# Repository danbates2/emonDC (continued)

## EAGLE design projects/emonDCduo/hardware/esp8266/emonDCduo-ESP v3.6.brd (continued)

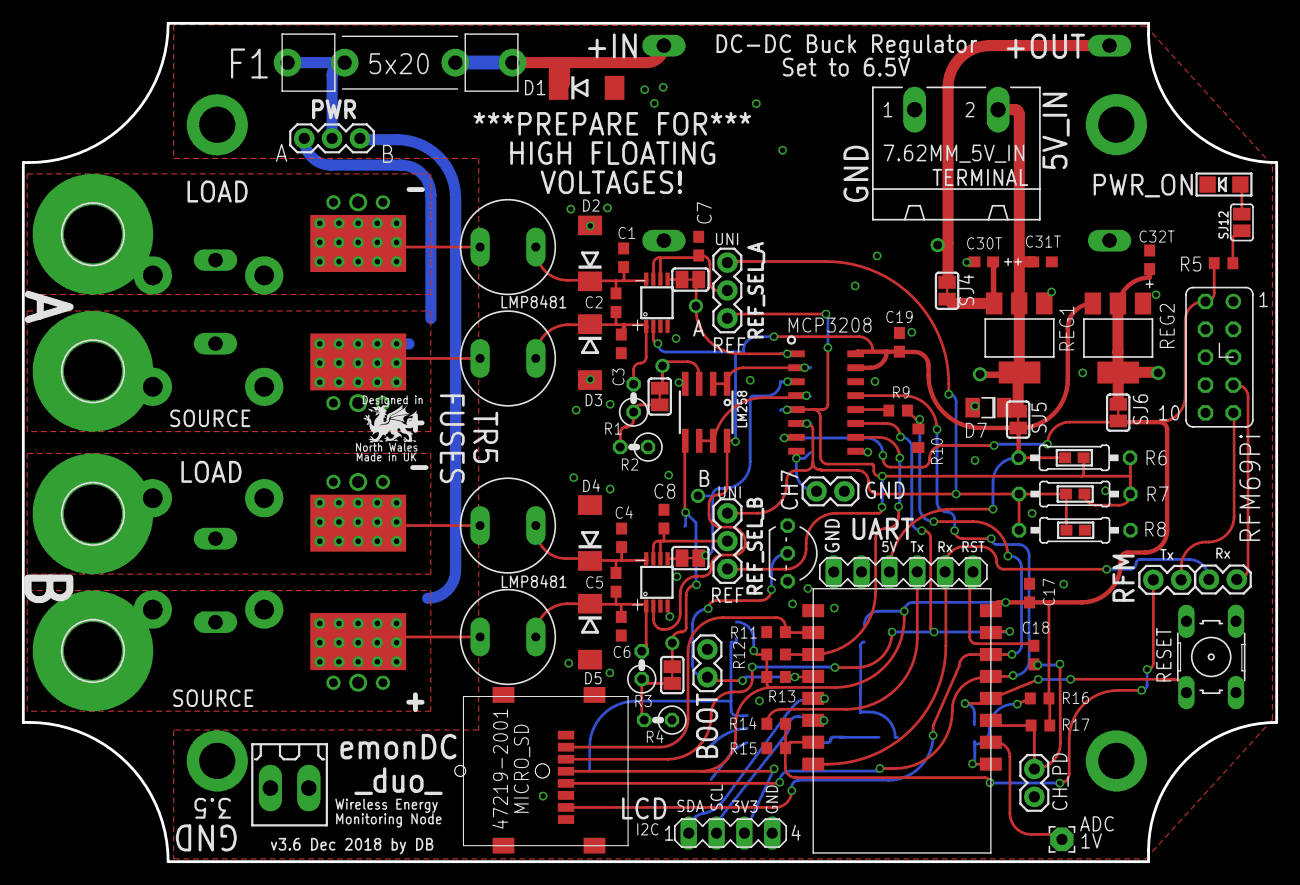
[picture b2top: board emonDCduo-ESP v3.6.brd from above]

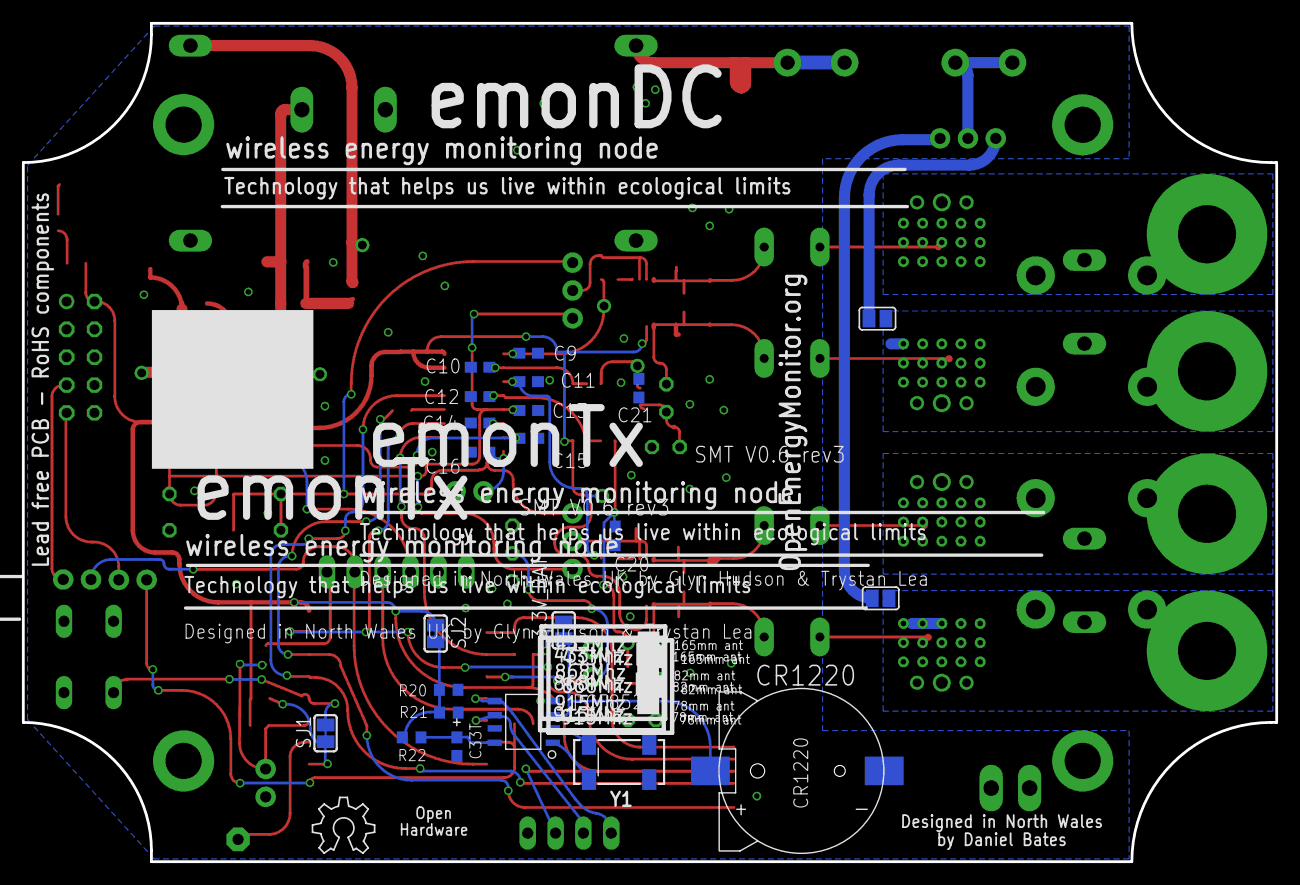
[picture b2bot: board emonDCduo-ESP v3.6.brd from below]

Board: 2 copper layers, 114.3 x 76.5 mm, 126 parts (24 on the bottom side), 60 nets.

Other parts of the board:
U$2, U$3: ALIGNMENT_STOP

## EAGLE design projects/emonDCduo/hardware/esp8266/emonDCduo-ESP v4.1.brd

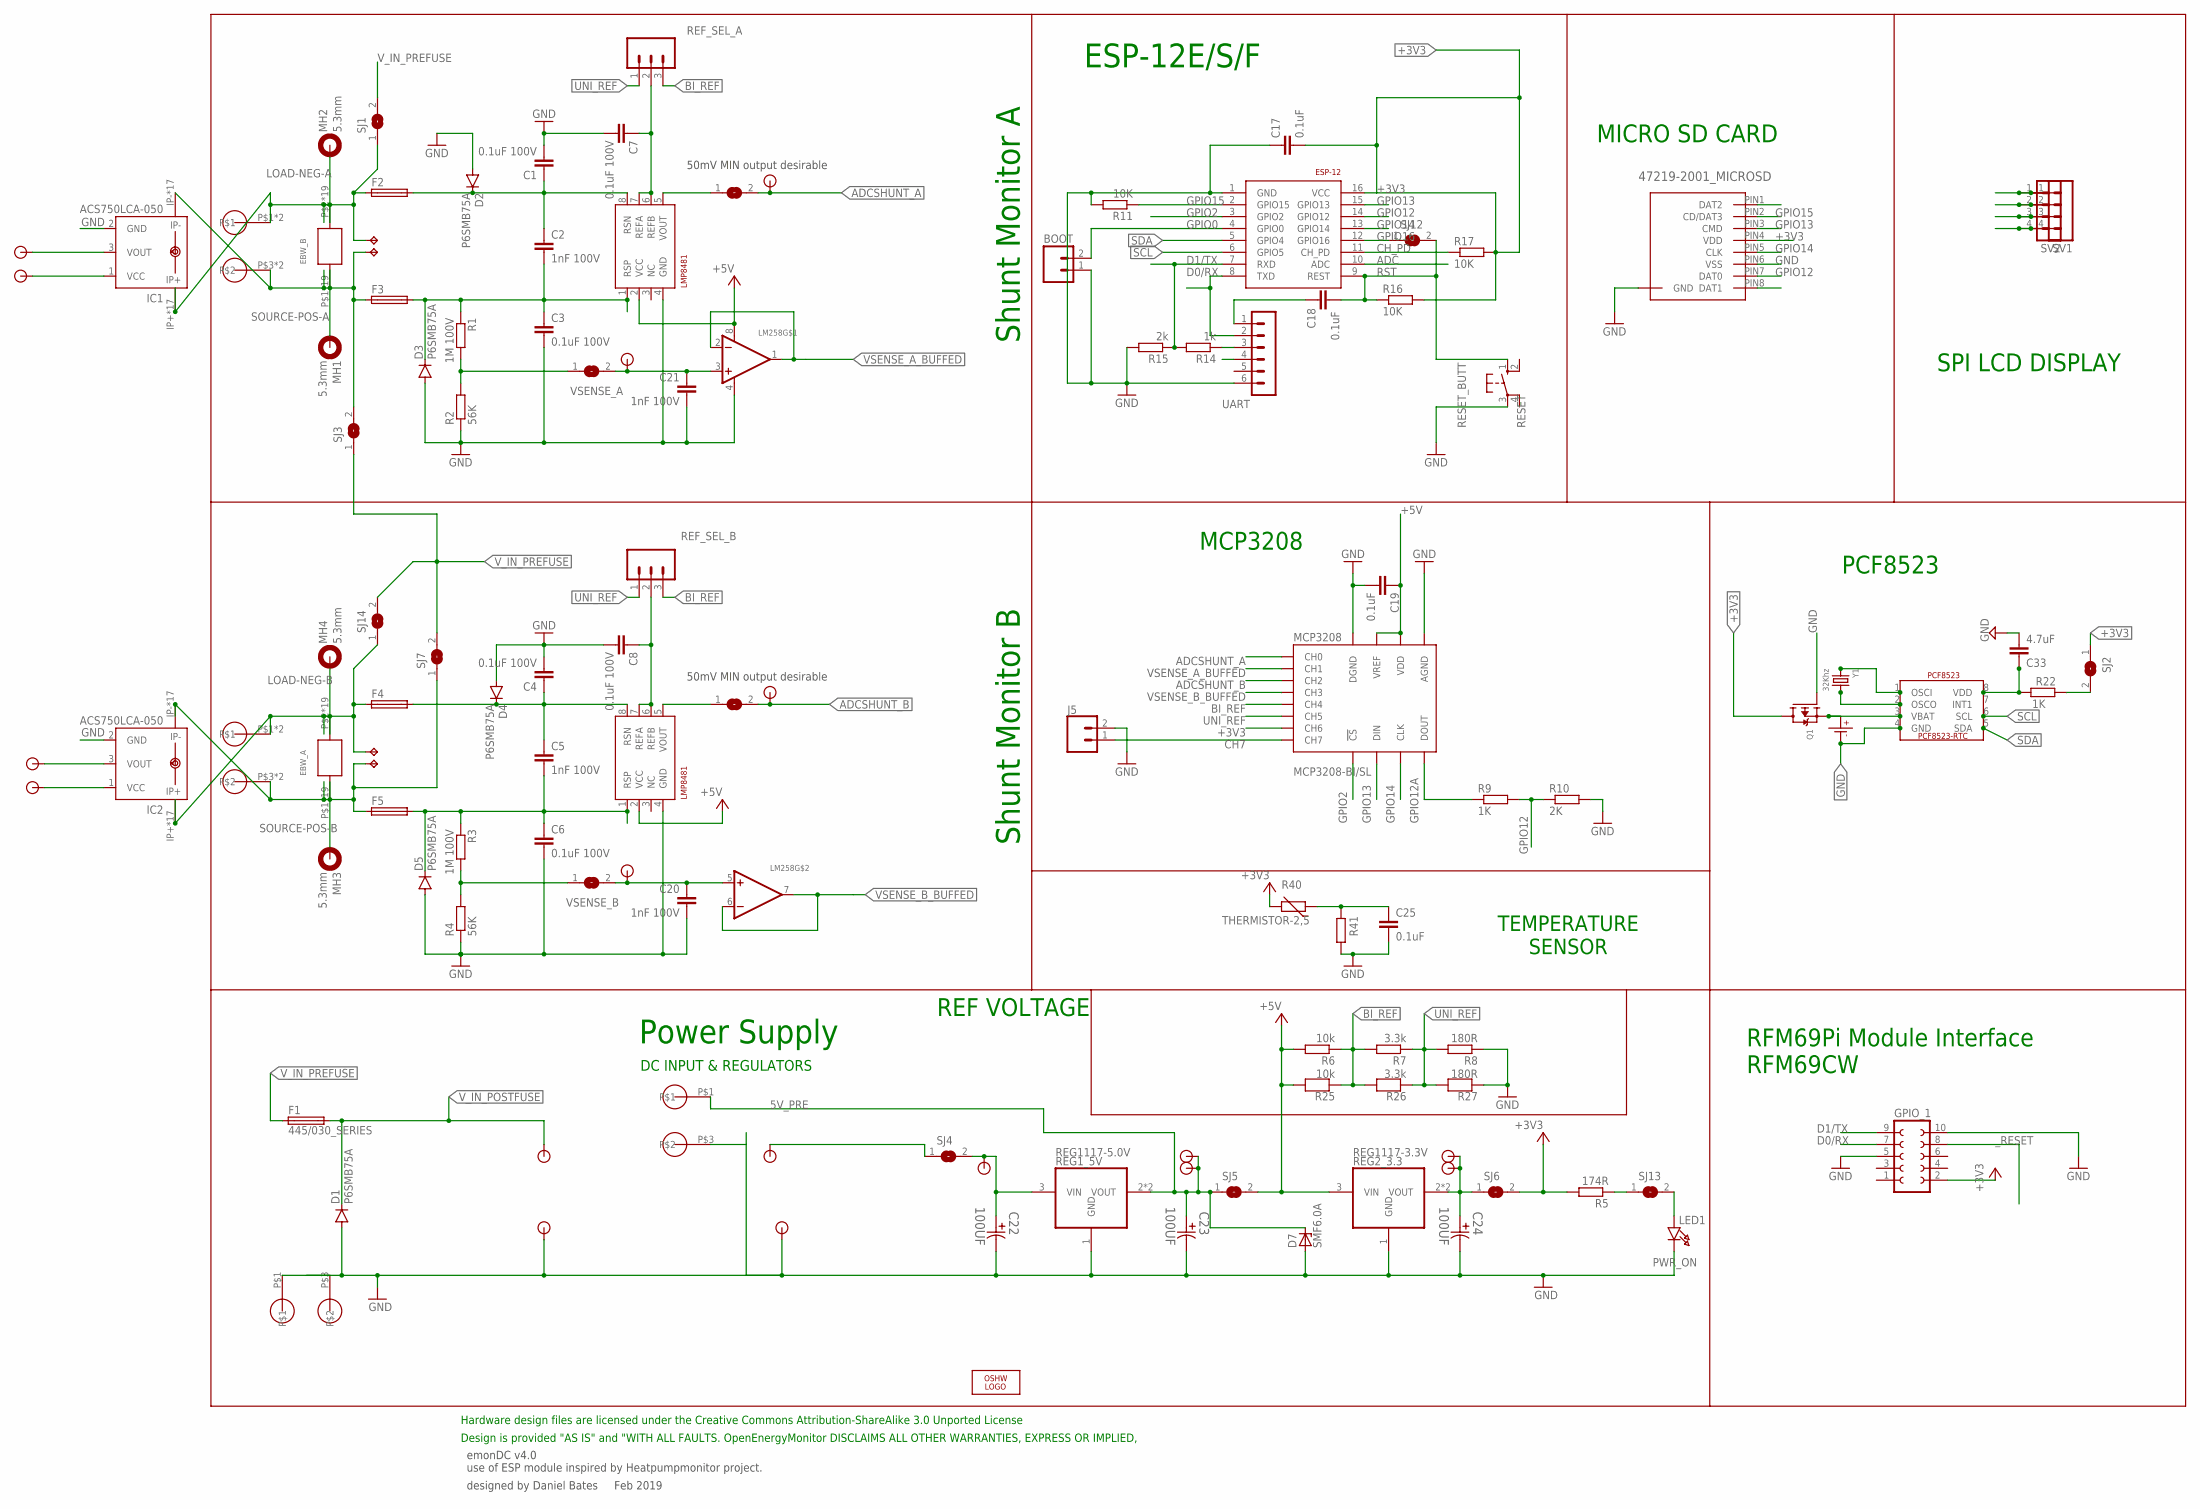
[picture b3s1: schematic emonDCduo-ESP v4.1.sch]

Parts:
BOOT: M02PTH; 1X02
C1, C3, C4, C6, C7, C8: 0.1uF 100V; C0805; MPN C1608X7S2A104K080AB
C2, C5, C20, C21: 1nF 100V; C0805; MPN C1608X7S2A104K080AB
C17, C18, C19, C25: 0.1uF; C0805
C22, C23, C24: 100UF; CAPAE530X610N
C33: 4.7uF; C0805
CR1220: CR1220SMD; MPN Harwin S8411-45R
D1: P6SMB75A; DO214AA
D2, D3, D4, D5: P6SMB75A; SMB
D7: SMF6.0A; SOD123F
EBW_A: EBW_SERIES_15.2MM
EBW_B: EBW_SERIES_15.2MM
ESP-12: ESP8266_ESP-12; ESP8266-ESP12
F1: 445/030_SERIES; 445/030_SERIES_LITTELFUSE
F2, F3, F4, F5: TR5
GPIO_1: FE05-2_RFM69PI_OUTLINERFM69PI; FE05-2_RFM69PI_OULTINE
IC1, IC2: ACS750LCA-050; ACS75050
J5: CONN_02; 1X02
LED1: PWR_ON; CHIPLED_1206
LM258: LM358; SOIC8_150MIL
LOGO1: OSHW_LOGO_6MILX0200-NT; OSHW_6X200_NOTEXT
MCP3208: MCP3208-BI/SL; SOIC16
MH1, MH2, MH3, MH4: 5.3mm; 5,3//11-PAD
MICRO_SD: 47219-2001_MICROSD
MOUNT_10.16_A, MOUNT_10.16_B: MOLEX_39970-003; 2/10,16
PCF8523: PCF8523_RTC; SOIC_8
Q1: MOSFET-P; SOT23-R
R1, R3: 1M 100V; 0207/2V; MPN MCMF006FF1004A50
R2, R4: 56K; 0207/2V; MPN MCMF006FF7502A50
R5: 174R; R0603
R6: 10k; 0207/10
R7: 3.3k; 0207/10
R8: 180R; 0207/10
R9: 1K; R0603; MPN MCWR06X5901FTL
R10: 2K; R0603; MPN MCWR06X5901FTL
R11, R16, R17: 10K; R0603
R14: 1k; R0603
R15: 2k; R0603
R22: 1K; R0603
R25: 10k; 0603
R26: 3.3k; 0603
R27: 180R; 0603
R40: THERMISTOR-2,5; RS-2,5
R41: R-EU_0207/2V; 0207/2V
REF_SEL_A: 455-1750-1-ND; 1X03; MPN 2212S-02SG-85
REF_SEL_B: 455-1750-1-ND; 1X03; MPN 2212S-02SG-85
REG1_5V: REG1117-5.0V; SOT223; MPN REG1117-5.0
REG2_3.3: REG1117-3.3V; SOT223; MPN REG1117-3.3
RESET: RESET_BUTT; B3F-10XX; MPN FSM4JH
SHUNTMON-A: LMP8481; S-PDSO-G08; MPN LMP8481MME-S/NOPB
SHUNTMON-B: LMP8481; S-PDSO-G08; MPN LMP8481MME-H/NOPB
SJ1, SJ3, SJ7, SJ14: SJW
SJ2, SJ4, SJ5, SJ6, SJ8, SJ9, SJ10, SJ11, SJ12, SJ13: SOLDERJUMPERCLOSED; SOLDERJUMPER_CLOSEDWIRE
SV1, SV2: MA04-1; MPN 2212S-04SG-85
TP8, TP9, TP10, TP11: TPPAD1-13Y; P1-13Y
U$1, U$4, U$5, U$6, U$7, U$8, U$9, U$14, U$15, U$16, U$17, U$18, U$19: TP0.8MM; TP0.8
U$2, U$3, U$10, U$11: 2212S-02SG-85; TP0.8_X2
U$12, U$13: 5MMBLOCK; 2/5.08
UART: UART; MA06-1
Y1: 32Khz; CRYSTAL_8X3.8

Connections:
3.3V_PRE: C24.1, REG2_3.3.2 (VOUT), REG2_3.3.4 (VOUT), SJ6.1, U$8.P$1, U$19.P$1
5V_PRE: C23.1, D7.C, REG1_5V.2 (VOUT), REG1_5V.4 (VOUT), SJ5.1, U$7.P$1, U$12.P$1, U$18.P$1
6.5V: C22.1, REG1_5V.3 (VIN), SJ4.2, U$9.P$1
+3V3: C17.2, ESP-12.16 (VCC), GPIO_1.2, MCP3208.7 (CH6), MICRO_SD.PIN4 (VDD), Q1.3 (D), R5.2, R16.2, R17.2, R40.2, SJ2.1, SJ6.2, SV1.3, SV2.3
+5V: C19.1, LM258.8 (V+), MCP3208.15 (VREF), MCP3208.16 (VDD), R6.2, R25.2, REG2_3.3.3 (VIN), SHUNTMON-A.2 (VCC), SHUNTMON-B.2 (VCC), SJ5.2, UART.4
ADC: C25.1, ESP-12.10 (ADC), R40.1, R41.2
ADCSHUNT_A: MCP3208.1 (CH0), SJ11.2, U$6.P$1
ADCSHUNT_B: MCP3208.3 (CH2), SJ10.2, U$5.P$1
BI_REF: MCP3208.5 (CH4), R6.1, R7.2, R25.1, R26.2, REF_SEL_A.3, REF_SEL_B.3
CH7: J5.1, MCP3208.8 (CH7)
CH_PD: ESP-12.11 (CH_PD), R17.1
D0/RX: ESP-12.8 (TXD), GPIO_1.7, UART.2
D1/TX: ESP-12.7 (RXD), GPIO_1.9, R14.2, R15.1
GND: BOOT.1, C1.2, C3.2, C4.2, C6.2, C7.2, C8.2, C17.1, C19.2, C20.2, C21.2, C22.2, C23.2, C24.2, C25.2, C33.2, CR1220.P- (P$-), D1.A, D2.A, D3.A, D4.A, D5.A, D7.A, ESP-12.1 (GND), GPIO_1.5, GPIO_1.10, IC1.2 (GND), IC2.2 (GND), J5.2, LED1.C, LM258.4 (V-), MCP3208.9 (DGND), MCP3208.14 (AGND), MICRO_SD.P$1 (GND), MICRO_SD.P$2 (GND), MICRO_SD.P$3 (GND), MICRO_SD.P$4 (GND), MICRO_SD.PIN6 (VSS), PCF8523.4 (GND), Q1.1 (G), R2.1, R4.1, R8.1, R10.2, R11.2, R15.2, R27.1, R41.1, REG1_5V.1 (GND), REG2_3.3.1 (GND), RESET.3, SHUNTMON-A.4 (GND), SHUNTMON-B.4 (GND), SV1.4, SV2.4, U$3.P$1, U$3.P$2, U$11.P$1, U$11.P$2, U$12.P$3, U$13.P$1, U$13.P$3, UART.6
GPIO0: BOOT.2, ESP-12.4 (GPIO0)
GPIO2: ESP-12.3 (GPIO2), MCP3208.10 (!CS)
GPIO12: ESP-12.14 (GPIO12), MICRO_SD.PIN7 (DAT0), R9.2, R10.1
GPIO12A: MCP3208.12 (DOUT), R9.1
GPIO13: ESP-12.15 (GPIO13), MCP3208.11 (DIN), MICRO_SD.PIN3 (CMD)
GPIO14: ESP-12.13 (GPIO14), MCP3208.13 (CLK), MICRO_SD.PIN5 (CLK)
GPIO15: ESP-12.2 (GPIO15), MICRO_SD.PIN2 (CD/DAT3), R11.1
GPIO16: ESP-12.12 (GPIO16), SJ12.1
LOAD-NEG-A: EBW_B.P$2, EBW_B.P$18, EBW_B.P$19, EBW_B.P$20, EBW_B.P$21, EBW_B.P$22, EBW_B.P$23, EBW_B.P$24, EBW_B.P$25, EBW_B.P$26, EBW_B.P$27, EBW_B.P$28, EBW_B.P$29, EBW_B.P$30, EBW_B.P$31, EBW_B.P$32, EBW_B.P$36, EBW_B.P$37, EBW_B.P$38, F2.1, IC1.IP+, IC1.IP+@2 (IP+), IC1.IP+@3 (IP+), IC1.IP+@4 (IP+), IC1.IP+@5 (IP+), IC1.IP+@6 (IP+), IC1.IP+@7 (IP+), IC1.IP+@8 (IP+), IC1.IP+@9 (IP+), IC1.IP+@10 (IP+), IC1.IP+@11 (IP+), IC1.IP+@12 (IP+), IC1.IP+@13 (IP+), IC1.IP+@14 (IP+), IC1.IP+@15 (IP+), IC1.IP+@16 (IP+), IC1.IP+@17 (IP+), MH2.B5,5, MOUNT_10.16_A.P$1, MOUNT_10.16_A.P$2, SJ1.1, TP11.TP
LOAD-NEG-A_T: C1.1, C2.1, D2.C, F2.2, SHUNTMON-A.8 (RSN)
LOAD-NEG-B: EBW_A.P$2, EBW_A.P$18, EBW_A.P$19, EBW_A.P$20, EBW_A.P$21, EBW_A.P$22, EBW_A.P$23, EBW_A.P$24, EBW_A.P$25, EBW_A.P$26, EBW_A.P$27, EBW_A.P$28, EBW_A.P$29, EBW_A.P$30, EBW_A.P$31, EBW_A.P$32, EBW_A.P$36, EBW_A.P$37, EBW_A.P$38, F4.1, IC2.IP+, IC2.IP+@2 (IP+), IC2.IP+@3 (IP+), IC2.IP+@4 (IP+), IC2.IP+@5 (IP+), IC2.IP+@6 (IP+), IC2.IP+@7 (IP+), IC2.IP+@8 (IP+), IC2.IP+@9 (IP+), IC2.IP+@10 (IP+), IC2.IP+@11 (IP+), IC2.IP+@12 (IP+), IC2.IP+@13 (IP+), IC2.IP+@14 (IP+), IC2.IP+@15 (IP+), IC2.IP+@16 (IP+), IC2.IP+@17 (IP+), MH4.B5,5, MOUNT_10.16_B.P$1, MOUNT_10.16_B.P$2, SJ14.1, TP9.TP
LOAD-NEG-B_T: C4.1, C5.1, D4.C, F4.2, SHUNTMON-B.8 (RSN)
unnamed: C18.1, UART.1
unnamed: R5.1, SJ13.1
unnamed: LED1.A, SJ13.2
unnamed: SHUNTMON-B.5 (VOUT), SJ10.1
unnamed: SHUNTMON-A.5 (VOUT), SJ11.1
unnamed: R14.1, UART.3
unnamed: PCF8523.2 (OSCO), Y1.P$4 (2)
unnamed: PCF8523.1 (OSCI), Y1.P$1 (1)
REF_A_INPUT: C7.1, REF_SEL_A.2, SHUNTMON-A.6 (REFB), SHUNTMON-A.7 (REFA)
REF_B_INPUT: C8.1, REF_SEL_B.2, SHUNTMON-B.6 (REFB), SHUNTMON-B.7 (REFA)
RST: C18.2, ESP-12.9 (REST), R16.1, RESET.1 (S), SJ12.2
SCL: ESP-12.6 (GPIO5), PCF8523.6 (SCL), SV1.2, SV2.2
SDA: ESP-12.5 (GPIO4), PCF8523.5 (SDA), SV1.1, SV2.1
SOURCE-POS-A: EBW_B.P$1, EBW_B.P$3, EBW_B.P$4, EBW_B.P$5, EBW_B.P$6, EBW_B.P$7, EBW_B.P$8, EBW_B.P$9, EBW_B.P$10, EBW_B.P$11, EBW_B.P$12, EBW_B.P$13, EBW_B.P$14, EBW_B.P$15, EBW_B.P$16, EBW_B.P$17, EBW_B.P$33, EBW_B.P$34, EBW_B.P$35, F3.1, IC1.IP-, IC1.IP-@2 (IP-), IC1.IP-@3 (IP-), IC1.IP-@4 (IP-), IC1.IP-@5 (IP-), IC1.IP-@6 (IP-), IC1.IP-@7 (IP-), IC1.IP-@8 (IP-), IC1.IP-@9 (IP-), IC1.IP-@10 (IP-), IC1.IP-@11 (IP-), IC1.IP-@12 (IP-), IC1.IP-@13 (IP-), IC1.IP-@14 (IP-), IC1.IP-@15 (IP-), IC1.IP-@16 (IP-), IC1.IP-@17 (IP-), MH1.B5,5, MOUNT_10.16_A.P$3, MOUNT_10.16_A.P$4, SJ3.2, TP10.TP
SOURCE-POS-A_T: C2.2, C3.1, D3.C, F3.2, R1.1, SHUNTMON-A.1 (RSP)
SOURCE-POS-B: EBW_A.P$1, EBW_A.P$3, EBW_A.P$4, EBW_A.P$5, EBW_A.P$6, EBW_A.P$7, EBW_A.P$8, EBW_A.P$9, EBW_A.P$10, EBW_A.P$11, EBW_A.P$12, EBW_A.P$13, EBW_A.P$14, EBW_A.P$15, EBW_A.P$16, EBW_A.P$17, EBW_A.P$33, EBW_A.P$34, EBW_A.P$35, F5.1, IC2.IP-, IC2.IP-@2 (IP-), IC2.IP-@3 (IP-), IC2.IP-@4 (IP-), IC2.IP-@5 (IP-), IC2.IP-@6 (IP-), IC2.IP-@7 (IP-), IC2.IP-@8 (IP-), IC2.IP-@9 (IP-), IC2.IP-@10 (IP-), IC2.IP-@11 (IP-), IC2.IP-@12 (IP-), IC2.IP-@13 (IP-), IC2.IP-@14 (IP-), IC2.IP-@15 (IP-), IC2.IP-@16 (IP-), IC2.IP-@17 (IP-), MH3.B5,5, MOUNT_10.16_B.P$3, MOUNT_10.16_B.P$4, SJ7.1, TP8.TP
SOURCE-POS-B_T: C5.2, C6.1, D5.C, F5.2, R3.1, SHUNTMON-B.1 (RSP)
UNI_REF: MCP3208.6 (CH5), R7.1, R8.2, R26.1, R27.2, REF_SEL_A.1, REF_SEL_B.1
VBAT: CR1220.P+ (P$+), PCF8523.3 (VBAT), Q1.2 (S)
VCC_ACS_A: IC1.1 (VCC), U$17.P$1
VCC_ACS_B: IC2.1 (VCC), U$15.P$1
VDD_PCF: C33.1, PCF8523.8 (VDD), R22.1
VDD_RTC_POSTJUMPER: R22.2, SJ2.2
VOUT_ACS_A: IC1.3 (VOUT), U$16.P$1
VOUT_ACS_B: IC2.3 (VOUT), U$14.P$1
VOUT_POST_SWITCHING: SJ4.1, U$10.P$1, U$10.P$2
VSENSE_A: R1.2, R2.2, SJ8.1
VSENSE_A_BUFFED: LM258.1 (OUT), LM258.2 (-IN), MCP3208.2 (CH1)
VSENSE_A_TP: C21.1, LM258.3 (+IN), SJ8.2, U$1.P$1
VSENSE_B: R3.2, R4.2, SJ9.1
VSENSE_B_BUFFED: LM258.6 (-IN), LM258.7 (OUT), MCP3208.4 (CH3)
VSENSE_B_TP: C20.1, LM258.5 (+IN), SJ9.2, U$4.P$1
V_IN_POSTFUSE: D1.C, F1.P$3 (2), F1.P$4 (2), U$2.P$1, U$2.P$2
V_IN_PREFUSE: F1.P$1 (1), F1.P$2 (1), SJ1.2, SJ3.1, SJ7.2, SJ14.2
_RESET: GPIO_1.8

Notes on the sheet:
emonDC v4.0 use of ESP module inspired by Heatpumpmonitor project.
designed by Daniel Bates Feb 2019
Power Supply
Design is provided "AS IS" and "WITH ALL FAULTS. OpenEnergyMonitor DISCLAIMS ALL OTHER WARRANTIES, EXPRESS OR IMPLIED,
Hardware design files are licensed under the Creative Commons Attribution-ShareAlike 3.0 Unported License
DC INPUT & REGULATORS
Shunt Monitor B
Shunt Monitor A
ESP-12E/S/F
MICRO SD CARD
RFM69Pi Module Interface RFM69CW
MCP3208
PCF8523
SPI LCD DISPLAY
TEMPERATURE SENSOR
50mV MIN output desirable
REF VOLTAGE

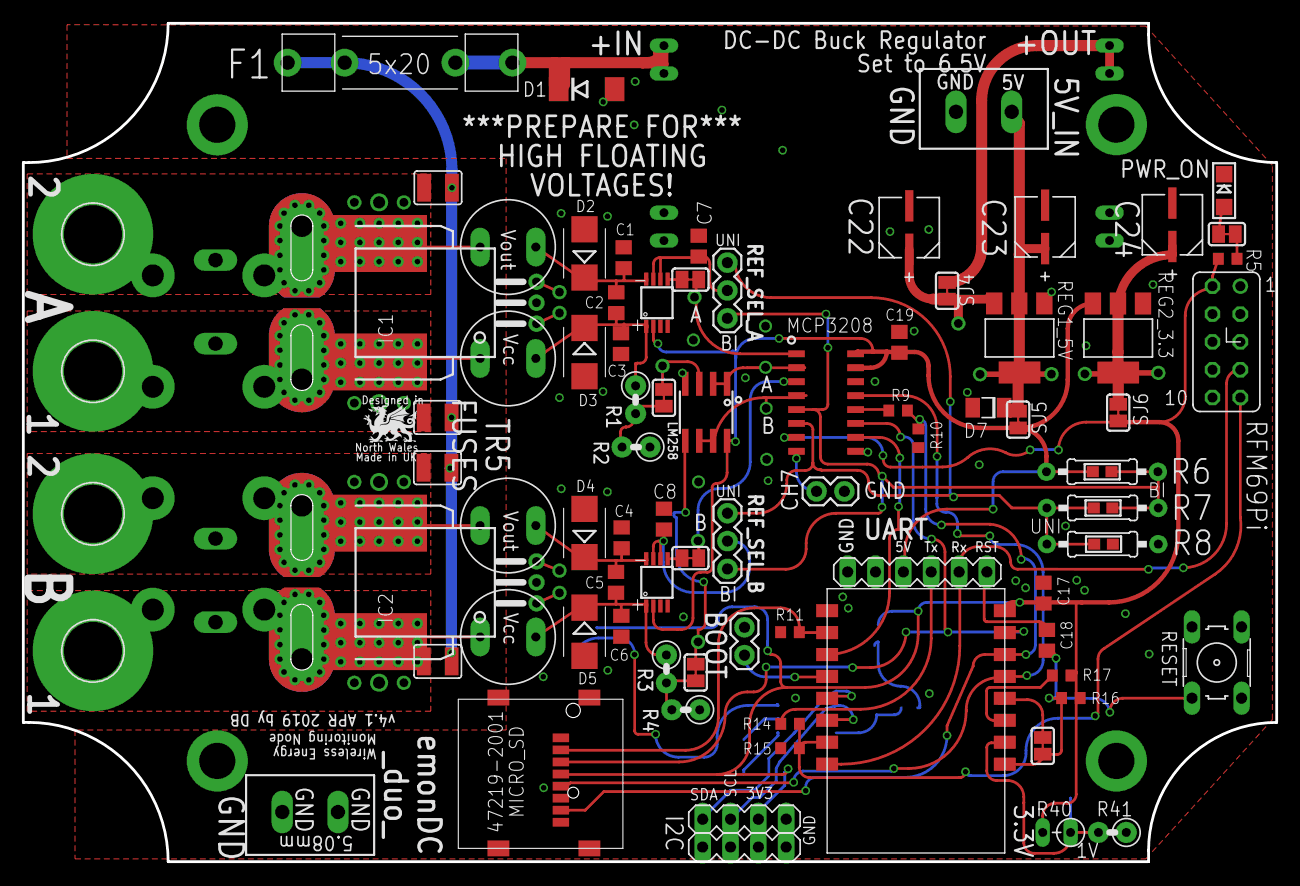
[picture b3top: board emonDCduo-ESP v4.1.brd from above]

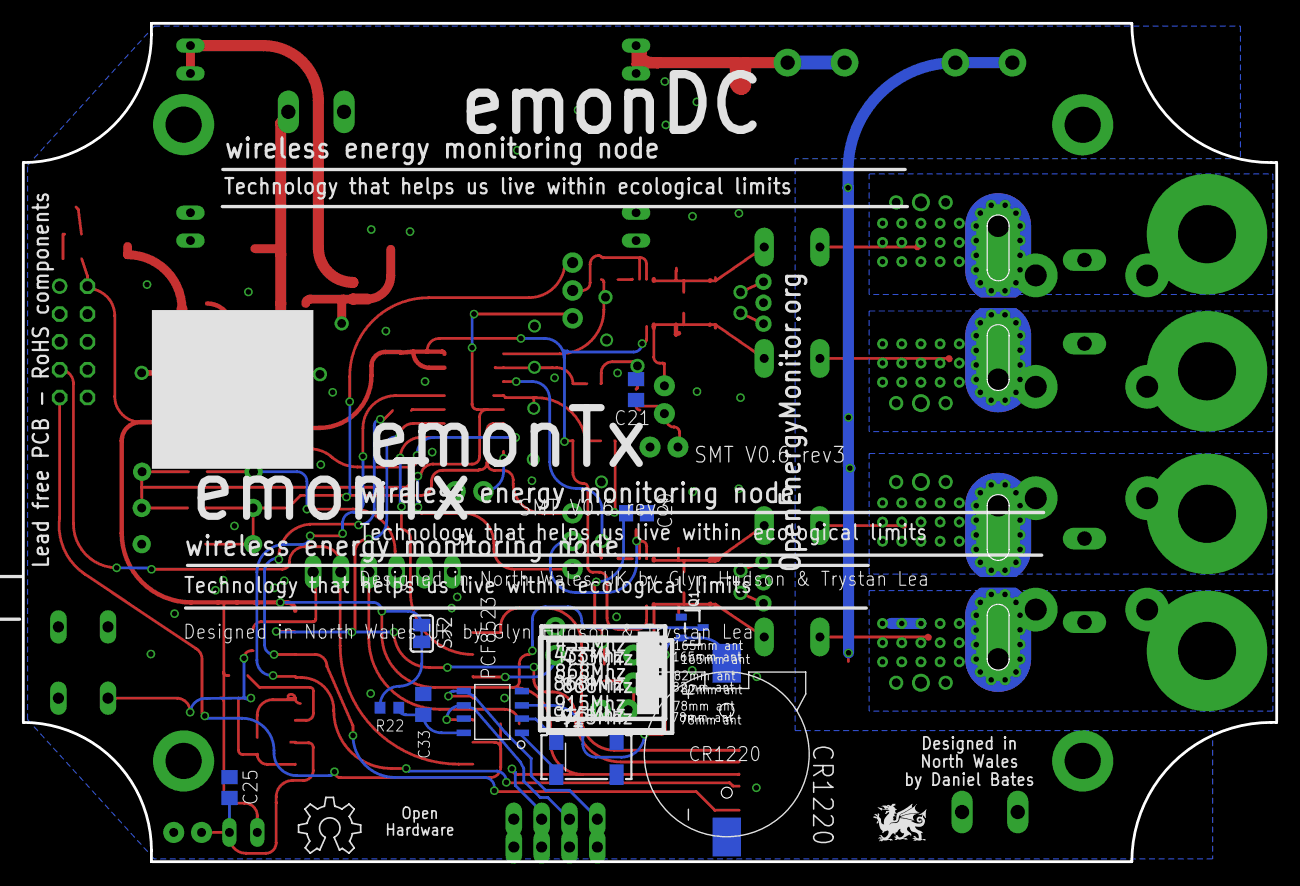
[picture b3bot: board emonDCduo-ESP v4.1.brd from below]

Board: 2 copper layers, 114.3 x 76.5 mm, 121 parts (12 on the bottom side), 60 nets.

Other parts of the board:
U$20: DRAGON_LOGO_NOTEXT

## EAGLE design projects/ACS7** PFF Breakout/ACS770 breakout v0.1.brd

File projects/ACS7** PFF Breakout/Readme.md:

[https://community.openenergymonitor.org/t/acs770-hall-effect-sensors/8675](https://community.openenergymonitor.org/t/acs770-hall-effect-sensors/8675)

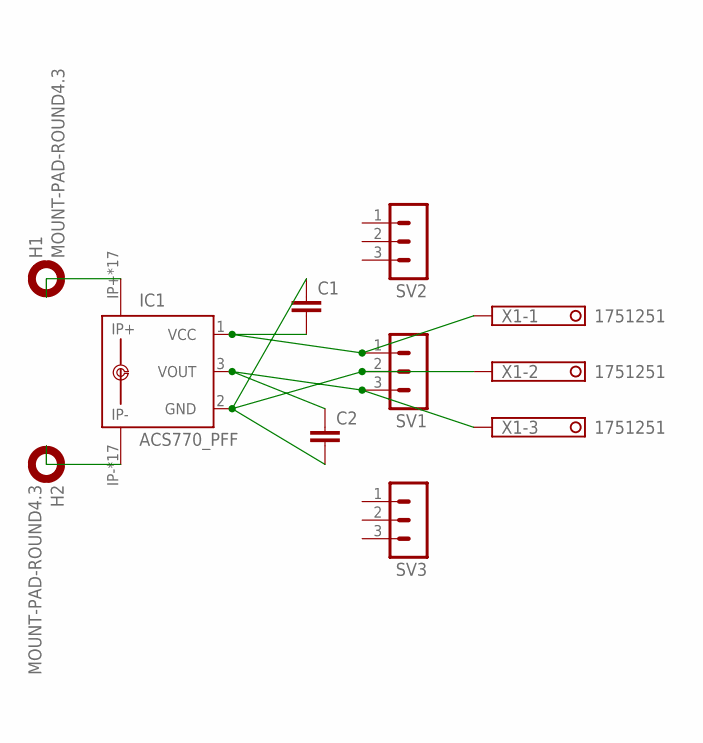
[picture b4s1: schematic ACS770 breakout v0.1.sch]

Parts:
C1, C2: C-EU025-025X050; C025-025X050
H1, H2: MOUNT-PAD-ROUND4.3; 4,3-PAD
IC1: ACS770_PFF; CB-PFF
SV1, SV2, SV3: MA03-1
X1: 1751251

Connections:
GND: C1.1, C2.2, IC1.2 (GND), SV1.2, X1.2
unnamed: C1.2, IC1.1 (VCC), SV1.1, X1.1
unnamed: C2.1, IC1.3 (VOUT), SV1.3, X1.3
unnamed: H2.B4,3, IC1.IP-, IC1.IP-@2 (IP-), IC1.IP-@3 (IP-), IC1.IP-@4 (IP-), IC1.IP-@5 (IP-), IC1.IP-@6 (IP-), IC1.IP-@7 (IP-), IC1.IP-@8 (IP-), IC1.IP-@9 (IP-), IC1.IP-@10 (IP-), IC1.IP-@11 (IP-), IC1.IP-@12 (IP-), IC1.IP-@13 (IP-), IC1.IP-@14 (IP-), IC1.IP-@15 (IP-), IC1.IP-@16 (IP-), IC1.IP-@17 (IP-)
unnamed: H1.B4,3, IC1.IP+, IC1.IP+@2 (IP+), IC1.IP+@3 (IP+), IC1.IP+@4 (IP+), IC1.IP+@5 (IP+), IC1.IP+@6 (IP+), IC1.IP+@7 (IP+), IC1.IP+@8 (IP+), IC1.IP+@9 (IP+), IC1.IP+@10 (IP+), IC1.IP+@11 (IP+), IC1.IP+@12 (IP+), IC1.IP+@13 (IP+), IC1.IP+@14 (IP+), IC1.IP+@15 (IP+), IC1.IP+@16 (IP+), IC1.IP+@17 (IP+)

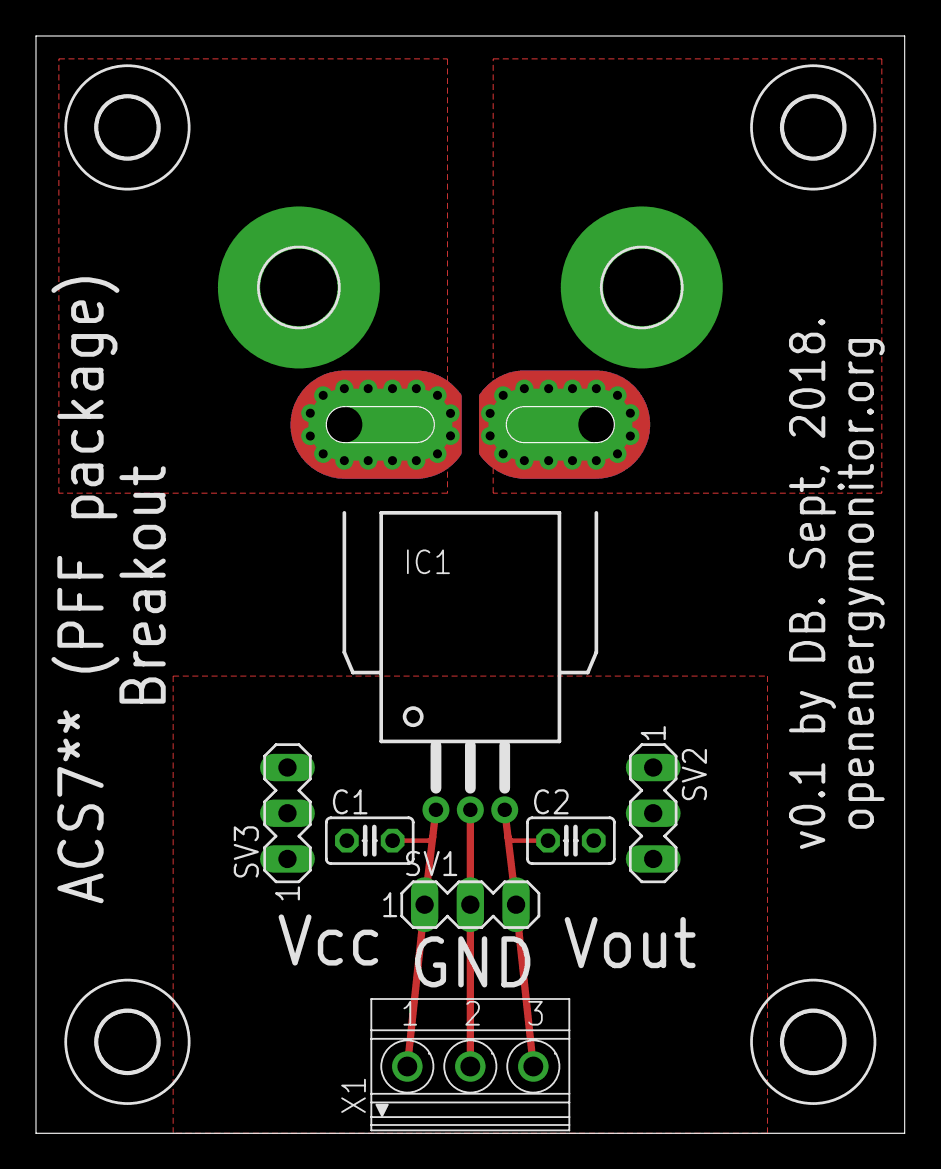
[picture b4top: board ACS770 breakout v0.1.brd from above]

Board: 2 copper layers, 48.3 x 61.0 mm, 13 parts (0 on the bottom side), 5 nets.

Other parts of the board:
U$1, U$2, U$3, U$4: 3,3

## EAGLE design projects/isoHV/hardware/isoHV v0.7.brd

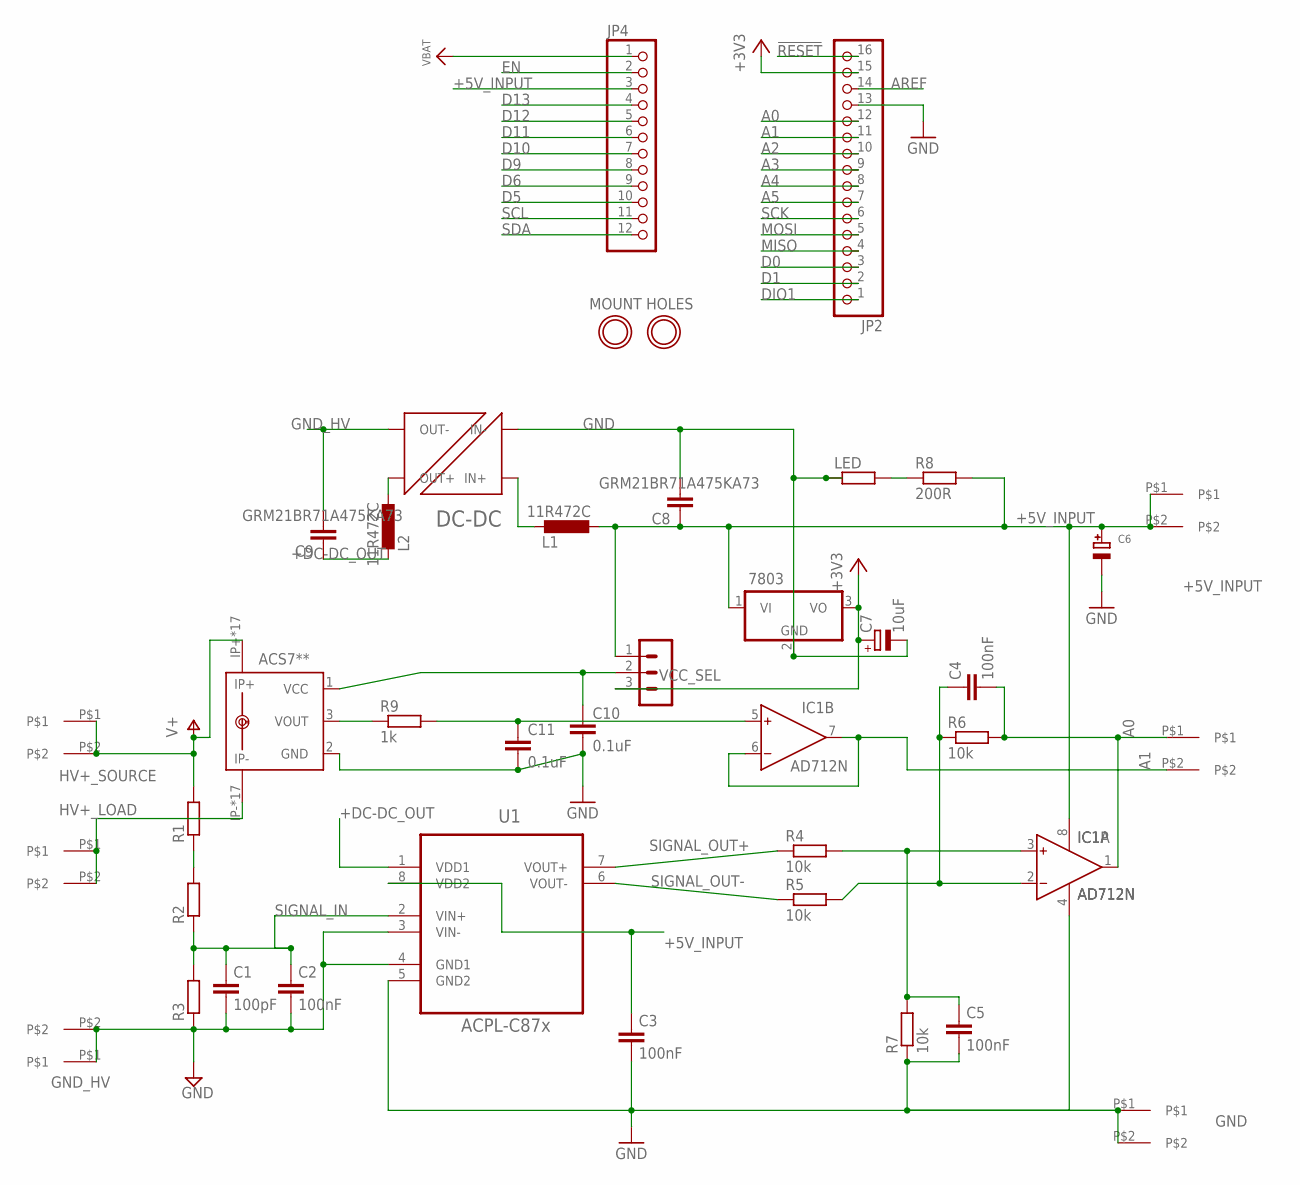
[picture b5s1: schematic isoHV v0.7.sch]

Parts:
7803: 7805TV; TO220V
ACS7**: ACS758KCB-150B-PFF-T; CB-PFF; MPN ACS7**
C1: 100pF; C025-025X050
C2, C3, C4, C5: 100nF; C025-025X050
C6: CAP_ELECTROLYTICPTH_3.5MMGRID_10MMDIA; CELEC_3.5MM_10MM
C7: 10uF; B45181A
C8: GRM21BR71A475KA73; C025-025X050
C9: GRM21BR71A475KA73; C025-050X050
C10, C11: 0.1uF; C025-025X050
IC1: AD712N; DIL08
JP2: HEADER-1X16ROUND; 1X16_ROUND
JP4: HEADER-1X12; 1X12_ROUND
L1, L2: 11R472C; 0204V
LED: R-EU_0204/2V; 0204V
R1, R2, R3: R-EU_0411/15; 0411/15
R4, R5, R6, R7: 10k; 0204/7
R8: 200R; 0204V
R9: 1k; 0204/7
U1: ACPL-C87x; SOIC127P1150X330-8N
U$1, U$2, U$3, U$4, U$5, U$6: 7.62MM_TERMINAL_BLOCK; 7.62MM
U$7: NXF1
U$12, U$13: MOUNTINGHOLE2.5; MOUNTINGHOLE_2.5_PLATED
VCC_SEL: MA03-1

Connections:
!RESET: JP2.16
+3V3: 7803.3 (VO), C7.+, JP2.15, VCC_SEL.3
+5V_INPUT: 7803.1 (VI), C3.1, C6.+, C8.1, IC1.8 (V+), JP4.3, L1.2, R8.2, U1.8 (VDD2), U$3.P$1, U$3.P$2, VCC_SEL.1
+DC-DC_OUT: C9.1, L2.1, U1.1 (VDD1)
A0: C4.2, IC1.1 (OUT), JP2.12, R6.2, U$5.P$1
A1: IC1.6 (IN-), IC1.7 (OUT), JP2.11, U$5.P$2
A2: JP2.10
A3: JP2.9
A4: JP2.8
A5: JP2.7
AREF: JP2.14
D0: JP2.3
D1: JP2.2
D5: JP4.10
D6: JP4.9
D9: JP4.8
D10: JP4.7
D11: JP4.6
D12: JP4.5
D13: JP4.4
DIO1: JP2.1
EN: JP4.2
GND: 7803.2 (GND), ACS7**.2 (GND), C3.2, C5.2, C6.-, C7.-, C8.2, C10.2, C11.2, IC1.4 (V-), JP2.13, LED.1, R7.1, U1.5 (GND2), U$4.P$1, U$4.P$2, U$7.P$1 (IN-)
GND_HV: C1.2, C2.2, C9.2, R3.1, U1.3 (VIN-), U1.4 (GND1), U$2.P$1, U$2.P$2, U$7.P$7 (OUT-)
HV+_LOAD: ACS7**.IP-, ACS7**.IP-@2 (IP-), ACS7**.IP-@3 (IP-), ACS7**.IP-@4 (IP-), ACS7**.IP-@5 (IP-), ACS7**.IP-@6 (IP-), ACS7**.IP-@7 (IP-), ACS7**.IP-@8 (IP-), ACS7**.IP-@9 (IP-), ACS7**.IP-@10 (IP-), ACS7**.IP-@11 (IP-), ACS7**.IP-@12 (IP-), ACS7**.IP-@13 (IP-), ACS7**.IP-@14 (IP-), ACS7**.IP-@15 (IP-), ACS7**.IP-@16 (IP-), ACS7**.IP-@17 (IP-), U$6.P$1, U$6.P$2
HV+_SOURCE: ACS7**.IP+, ACS7**.IP+@2 (IP+), ACS7**.IP+@3 (IP+), ACS7**.IP+@4 (IP+), ACS7**.IP+@5 (IP+), ACS7**.IP+@6 (IP+), ACS7**.IP+@7 (IP+), ACS7**.IP+@8 (IP+), ACS7**.IP+@9 (IP+), ACS7**.IP+@10 (IP+), ACS7**.IP+@11 (IP+), ACS7**.IP+@12 (IP+), ACS7**.IP+@13 (IP+), ACS7**.IP+@14 (IP+), ACS7**.IP+@15 (IP+), ACS7**.IP+@16 (IP+), ACS7**.IP+@17 (IP+), R1.2, U$1.P$1, U$1.P$2
MISO: JP2.4
MOSI: JP2.5
unnamed: C5.1, IC1.3 (IN+), R4.2, R7.2
unnamed: R1.1, R2.2
unnamed: ACS7**.1 (VCC), C10.1, VCC_SEL.2
unnamed: LED.2, R8.1
unnamed: C4.1, IC1.2 (IN-), R5.2, R6.1
unnamed: C11.1, IC1.5 (IN+), R9.2
unnamed: L1.1, U$7.P$3 (IN+)
unnamed: L2.2, U$7.P$8 (OUT+)
unnamed: ACS7**.3 (VOUT), R9.1
SCK: JP2.6
SCL: JP4.11
SDA: JP4.12
SIGNAL_IN: C1.1, C2.1, R2.1, R3.2, U1.2 (VIN+)
SIGNAL_OUT+: R4.1, U1.7 (VOUT+)
SIGNAL_OUT-: R5.1, U1.6 (VOUT-)
VBAT: JP4.1

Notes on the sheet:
MOUNT HOLES

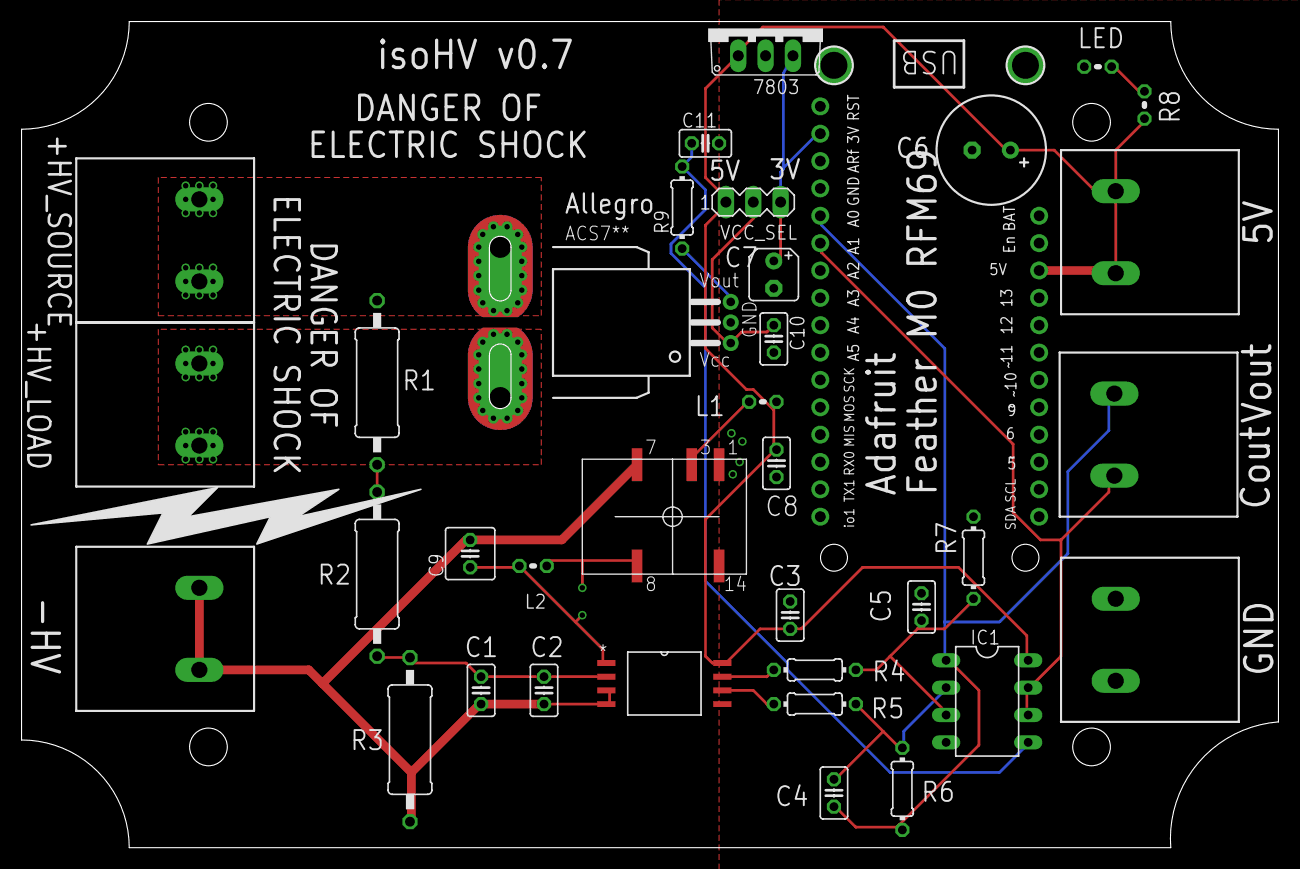
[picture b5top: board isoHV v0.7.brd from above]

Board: 2 copper layers, 116.7 x 76.7 mm, 39 parts (0 on the bottom side), 21 nets.
